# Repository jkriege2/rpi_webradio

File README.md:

# rpi_webradio
webradio with GUI for TFT on a Raspberry PI.

This project is a GUI (own library, using cairo as a graphics backend), which will allow to control mpd via buttons, rotary encoders and possibly a touch-screen.

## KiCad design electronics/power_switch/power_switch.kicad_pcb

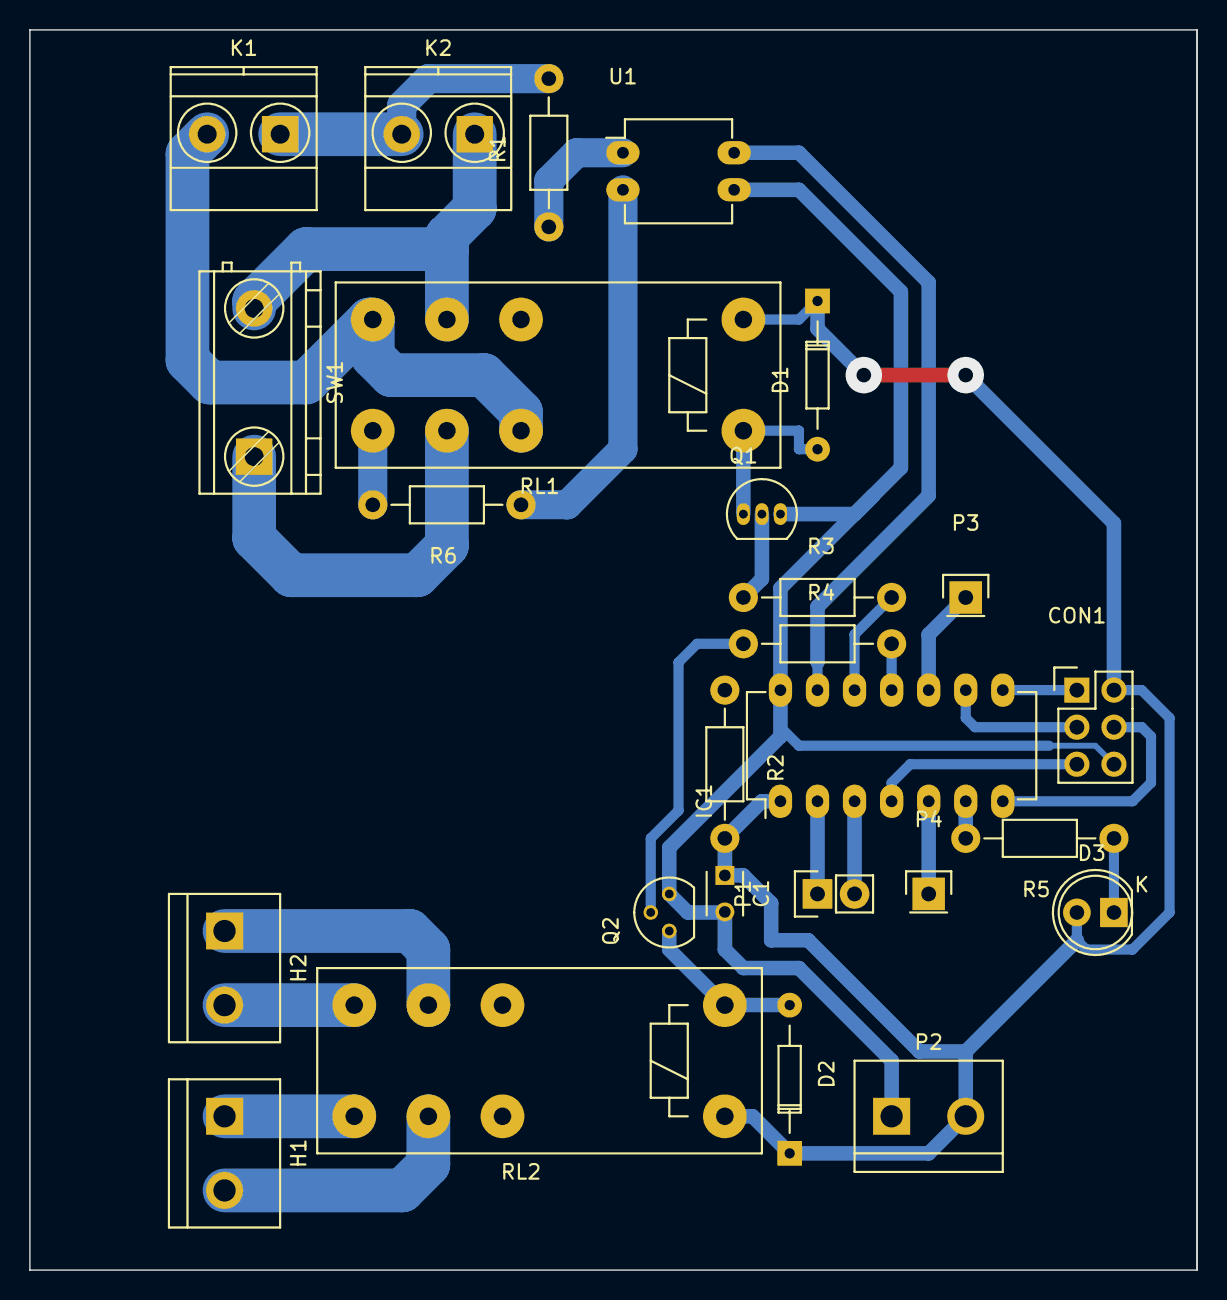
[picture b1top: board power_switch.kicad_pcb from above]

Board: 2 copper layers, 80.0 x 85.0 mm, 26 parts (0 on the bottom side), 30 nets.

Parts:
C1: 100nF; C_Disc_D3_P2.5
CON1: AVR-ISP-6; Pin_Header_Straight_2x03
D1, D2: D; Diode_DO-35_SOD27_Horizontal_RM10
D3: LED; LED-5MM
H1, H2: screw_terminal_2x01; bornier2
IC1: ATTINY84-P; DIP-14_W7.62mm_LongPads
K1: WALLPLUG_NOEARTH_220V; TerminalBlock_Pheonix_MKDS1.5-2pol
K2: WALLSOCKET_NOEARTH_220V; TerminalBlock_Pheonix_MKDS1.5-2pol
P1: CONN_01X02; Pin_Header_Straight_1x02
P2: 5V=; bornier2
P3, P4: CONN_01X01; Pin_Header_Straight_1x01
Q1: BC548; TO-92_Inline_Narrow_Oval
Q2: BC548; TO-92_Molded_Narrow
R1, R6: 47k; Resistor_Horizontal_RM10mm
R2: 1k; Resistor_Horizontal_RM10mm
R3, R4: 10k; Resistor_Horizontal_RM10mm
R5: 220R; Resistor_Horizontal_RM10mm
RL1, RL2: FINDER-40.52; Relay_DPDT_Schrack-RT2_RM5mm
SW1: SPST; TerminalBlock_RND-205-00243_RM10.16mm_2pol
U1: LTV-814; DIP-4_W7.62mm_LongPads

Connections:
+5V: C1.1, CON1.2, D1.1, D2.1, D3.2, IC1.1, P2.2, R2.2, RL1.A2, RL2.A1
GND: C1.2, CON1.6, IC1.14, P2.1, Q1.3, Q2.3, U1.3
unnamed: CON1.1, IC1.8
unnamed: CON1.3, IC1.9
unnamed: CON1.4, IC1.7
unnamed: CON1.5, IC1.4
unnamed: D1.2, Q1.1, RL1.A1
unnamed: D2.2, Q2.1, RL2.A2
unnamed: D3.1, R5.1
unnamed: H1.1, RL2.14
unnamed: H1.2, RL2.11
unnamed: H2.1, RL2.21
unnamed: H2.2, RL2.24
unnamed: IC1.2, P1.1
unnamed: IC1.3, P1.2
unnamed: IC1.5, P4.1
unnamed: IC1.6, R5.2
unnamed: IC1.10, P3.1
unnamed: IC1.11, R4.2
unnamed: IC1.12, R3.2
unnamed: IC1.13, R2.1, U1.4
unnamed: K1.1, K2.2, R1.2
unnamed: K1.2, RL1.12, RL1.24
unnamed: K2.1, RL1.21, SW1.2
unnamed: Q1.2, R3.1
unnamed: Q2.2, R4.1
unnamed: R1.1, U1.1
unnamed: R6.1, U1.2
unnamed: R6.2, RL1.14
unnamed: RL1.11, SW1.1

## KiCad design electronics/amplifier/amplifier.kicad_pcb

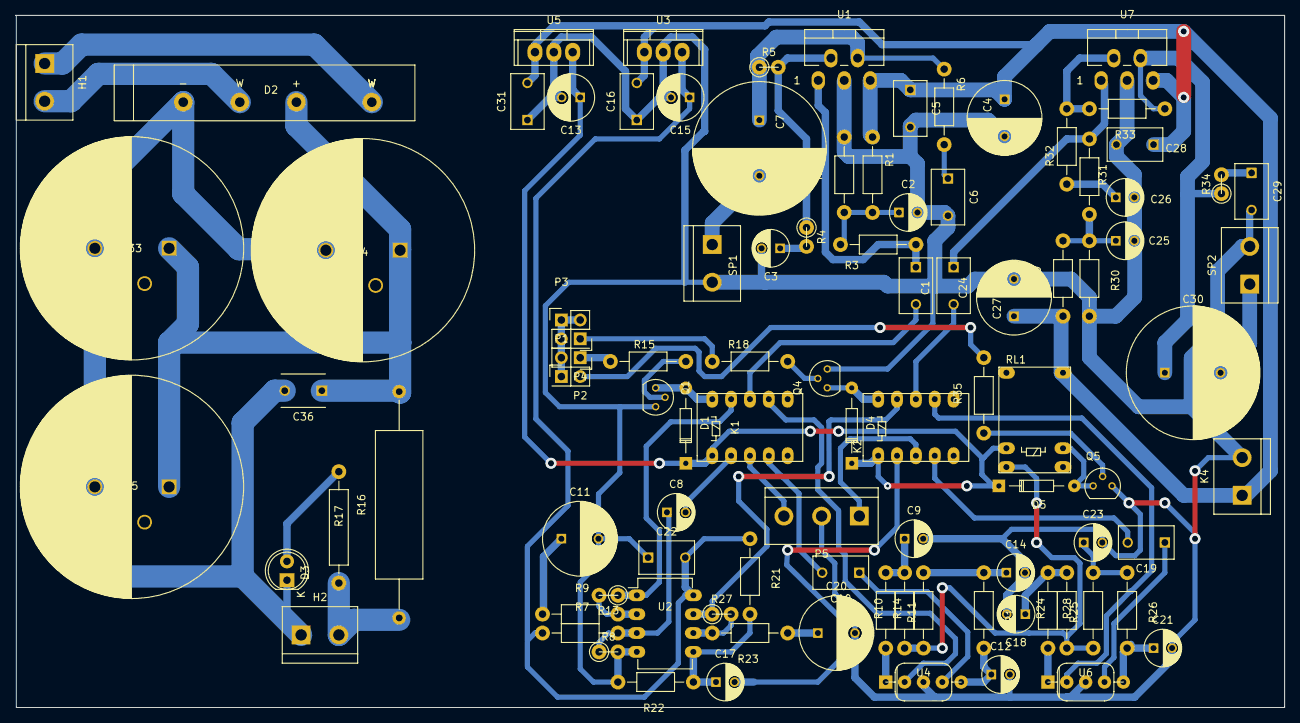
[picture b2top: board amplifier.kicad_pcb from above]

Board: 2 copper layers, 170.9 x 93.2 mm, 96 parts (0 on the bottom side), 63 nets.

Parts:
C1, C5, C6, C16, C22, C24, C28, C29, C31: 100nF; C_Disc_D7.5_P5
C2, C3, C9, C14, C18, C21, C23, C25, C26: 10µF; C_Radial_D5_L6_P2.5
C4, C27: 100µF; C_Radial_D10_L13_P5
C7, C30: 4700µF; C_Radial_D18_L36_P7.5
C8, C17: 2.2µF; C_Radial_D5_L11_P2.5
C10, C19: 68nF; C_Disc_D7.5_P5
C11, C20: 220µF; C_Radial_D10_L13_P5
C12: 10µF; C_Radial_D5_L11_P2.5
C13, C15: 100µF; C_Radial_D6.3_L11.2_P2.5
C33, C34, C35: 2200µF; C_Radial_D30_L51_P10_3pin
C36: 100nF; C_Disc_D6_P5
D1, D4, D5: 1N4148; Diode_DO-35_SOD27_Horizontal_RM10
D2: B40C5000; Diode_Bridge_32x5.7
D3: LED; LED-5MM
H1, H2: screw_terminal_2x01; bornier2
K1, K2: FRT5_separated; Relay_DPDT_FRT5
K4: screw_terminal_2x01; bornier2
P1, P2, P3, P4: CONN_02X01; Pin_Header_Straight_2x01
P5: CONN_01X03; bornier3
Q1, Q4, Q5: BC548; TO-92_Molded_Narrow
R1, R2, R6, R29, R30: 2k2; Resistor_Horizontal_RM10mm
R3, R31: 330k; Resistor_Horizontal_RM10mm
R4, R8: 22k; Resistor_Vertical_RM2.5mm
R5: 220k; Resistor_Vertical_RM2.5mm
R7, R21, R22, R32: 22k; Resistor_Horizontal_RM10mm
R9, R23: 220R; Resistor_Horizontal_RM10mm
R10, R24: 8k2; Resistor_Horizontal_RM10mm
R11, R25: 47k; Resistor_Horizontal_RM10mm
R12, R14, R26, R28: 1k2; Resistor_Horizontal_RM10mm
R13, R27: 820R; Resistor_Vertical_RM2.5mm
R15, R18, R35: 10k; Resistor_Horizontal_RM10mm
R16: 1R; Resistor_Ceramic_Horizontal_L25mm-W6.4mm-H6.4mm-p30mm
R17: 1k5; Resistor_Horizontal_RM15mm
R33: 220k; Resistor_Horizontal_RM10mm
R34: 2k2; Resistor_Vertical_RM2.5mm
RL1: TIANBO-HJR-4102-L; Relay_SPDT_HJR-4102
SP1, SP2: SPEAKER; bornier2
U1, U7: LM1875; Pentawatt_Neutral_Staggered_Verical_TO220-5-T05D
U2: TL082; DIP-8_W7.62mm_LongPads
U3: LM7815CT; TO-220
U4, U6: CK6418; VALVE-MINI_PENTODE_LINEAR
U5: LM7805CT; TO-220

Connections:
+5V: C13.1, D1.1, D4.1, D5.1, K1.1, K2.1, RL1.5, U5.3
+15V: C15.1, C22.2, R7.1, R21.1, U2.8, U3.3
+24V: C4.1, C5.1, C16.2, C27.1, C28.1, C31.2, K4.1, R1.1, R29.1, RL1.12, U1.5, U3.1, U5.1, U7.5
GND: C2.2, C3.2, C4.2, C5.2, C6.2, C9.2, C11.2, C12.2, C13.2, C14.2, C15.2, C16.1, C18.2, C20.2, C21.2, C22.1, C23.2, C25.2, C26.2, C27.2, C28.2, C29.2, C31.1, K4.2, P5.2, Q1.3, Q4.3, Q5.3, R2.2, R8.2, R22.2, R30.2, SP1.2, SP2.2, U1.3, U2.4, U3.2, U4.3, U5.2, U6.3, U7.3
unnamed: C1.1, R3.1, U1.1
unnamed: C1.2, K1.8
unnamed: C2.1, R1.2, R2.1, R3.2
unnamed: C3.1, R4.2
unnamed: C6.1, R6.2
unnamed: C7.1, R5.1, R6.1, U1.4
unnamed: C7.2, SP1.1
unnamed: C8.1, R7.2, R8.1, U2.3
unnamed: C8.2, K1.2
unnamed: C9.1, R10.2, R11.1
unnamed: C10.1, U4.4
unnamed: C10.2, K1.4
unnamed: C11.1, R9.1
unnamed: C12.1, R12.2, U4.5
unnamed: C14.1, R12.1, R14.2
unnamed: C17.1, R21.2, R22.1, U2.5
unnamed: C17.2, K2.2
unnamed: C18.1, R24.2, R25.1
unnamed: C19.1, U6.4
unnamed: C19.2, K2.4
unnamed: C20.1, R23.1
unnamed: C21.1, R26.2, U6.5
unnamed: C23.1, R26.1, R28.2
unnamed: C24.1, R31.1, U7.1
unnamed: C24.2, K2.8
unnamed: C25.1, R29.2, R30.1, R31.2
unnamed: C26.1, R32.2
unnamed: C29.1, R34.2
unnamed: C30.1, R33.1, R34.1, U7.4
unnamed: C30.2, SP2.1
unnamed: C33.1, C34.1, C35.1, C36.1, D2.3, R16.2
unnamed: C33.2, C34.2, C35.2, C36.2, D2.1, D3.1, H2.1
unnamed: D1.2, K1.10, Q1.1
unnamed: D2.2, H1.1
unnamed: D2.4, H1.2
unnamed: D3.2, R17.2
unnamed: D4.2, K2.10, Q4.1
unnamed: D5.2, Q5.1, RL1.8
unnamed: H2.2, R16.1, R17.1
unnamed: K1.3, P5.3
unnamed: K1.7, U4.2
unnamed: K1.9, R13.1, U2.1
unnamed: K2.3, P5.1
unnamed: K2.7, U6.2
unnamed: K2.9, R27.1, U2.7
unnamed: P1.2, R35.2
unnamed: P2.1, R15.2
unnamed: P4.1, R18.2
unnamed: Q1.2, R15.1
unnamed: Q4.2, R18.1
unnamed: Q5.2, R35.1
unnamed: R4.1, R5.2, U1.2
unnamed: R11.2, U4.1
unnamed: R9.2, R13.2, U2.2
unnamed: R23.2, R27.2, U2.6
unnamed: R25.2, U6.1
unnamed: R32.1, R33.2, U7.2
RELAIS: P1.1, P2.2, P3.1, P3.2, P4.2
VPP: R10.1, R14.1, R24.1, R28.1, RL1.6

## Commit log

2015-08-24 * improved plotting * added widget CGScreen, which represents full screen * added simple event system with broadcasting until event is accepted (otherwise to all widgets in the tree)
2015-08-30 - added progress bar - added list widget - improved CGFontProps classes
2015-09-13 * added new widgets * restructured repo
2015-09-13 start
2015-09-13 started implementing events for RPi input pins, using WiringLib
2015-09-14 * added event handling for scrolling with rotary encoders * added double-clicks to buttons * encapsuled WiringPi functionality in rpi_tools.h
2015-09-23 * added focus system to CGWidget * changed interface toCGPalette to use const methods now!
2015-10-25 * some refactoring * added CGTabbedMultiScreens, which is like CGMultiScreens, but with an additional tab-tar * added CGTabMixin, which can be used to build widgets that contain a tab-bar
2015-11-21 several improvements
2015-11-21 started using boost
2015-11-28 added CGLayout
2015-12-01 added makefile fir lib-subproject, modified Makefile in test_widgets accordingly
2015-12-02 lib: added CGSymbol, CGTwoStateImage lib: improved scaling of CGMultiScreen children added new subproject "webradio_gui" for the actual GUI
2016-01-28 - diverse improvements - added base class CGTreeBase for tree widgets - started to write CGDirectoryTreeWidget - corrected path to crontab in install-script
2016-01-28 - bugfix - new stations
2016-01-28 - radio stations are sorted now automatically and mainscreen-selection is stored in INI - creating INI-file from argv[0] + proper storage - improved determination of home-directory
2016-01-29 - CGListWidget is now a template, so custom Itemdata can be specified - webradio_stations.ini is now UTF8
2016-01-29 added test for mpd_tools
2016-01-29 added MP3 listing to webplayer
2016-01-30 - improved mpdtools stability - improved music player screen - restart playing last song (from start), when changing between Radio- and Music-tabs
2016-01-30 - softblink LED-button - buttons for random and repeat - playing playlists - rotatable screen (by 90°)
2016-01-31 - marquee label added
2016-01-31 - layout improved (better auto-layout) - music player remembers last tree-contents - radio-screen shows more data/nicer formatted - added photos
2016-02-12 added Logo
2016-02-12 rotated logo
2016-02-12 - split libraries - add precompiled headers - diverse updates
2016-05-06 initial design for speaker box
2016-05-07 2. Design für Lautsprecherboxen
2016-05-07 2-Wege Design
2016-09-03 updated speaker box design + started tube amplifier schematic
2016-09-04 improved tube amplifier schematic
2016-09-04 moved files to subdir
2016-09-04 added power supply circuit
2016-09-11 Entwurf für Gehäuse
2016-09-11 #IM Update Schaltungen
2016-09-11 Plan für Gehäusevorderseite
2016-09-13 added footprint for mini valve
2016-09-15 added valve symbols and 3D model
2016-09-15 started PCB for AMPLIFIER
2016-09-16 added resistors, small
2016-09-16 update symbol
2016-09-16 added symbols
2016-09-16 fixed 3d symbols
2016-09-17 added 3dmodels etc.
2016-09-17 changed symbols
2016-09-18 diverse libs
2016-09-18 finished amplifier PCB
2016-09-18 completed switch PCB
2016-09-20 changed some parts
2016-09-21 changed screw terminal
2016-09-23 added diode 3d models
2020-03-28 diverse makefile fixes
2020-04-02 some fixes
2020-04-02 minor fix
2020-04-03 switched build system to cmake + reorganization
2020-04-10 precompiled headers now suppert -fPic
